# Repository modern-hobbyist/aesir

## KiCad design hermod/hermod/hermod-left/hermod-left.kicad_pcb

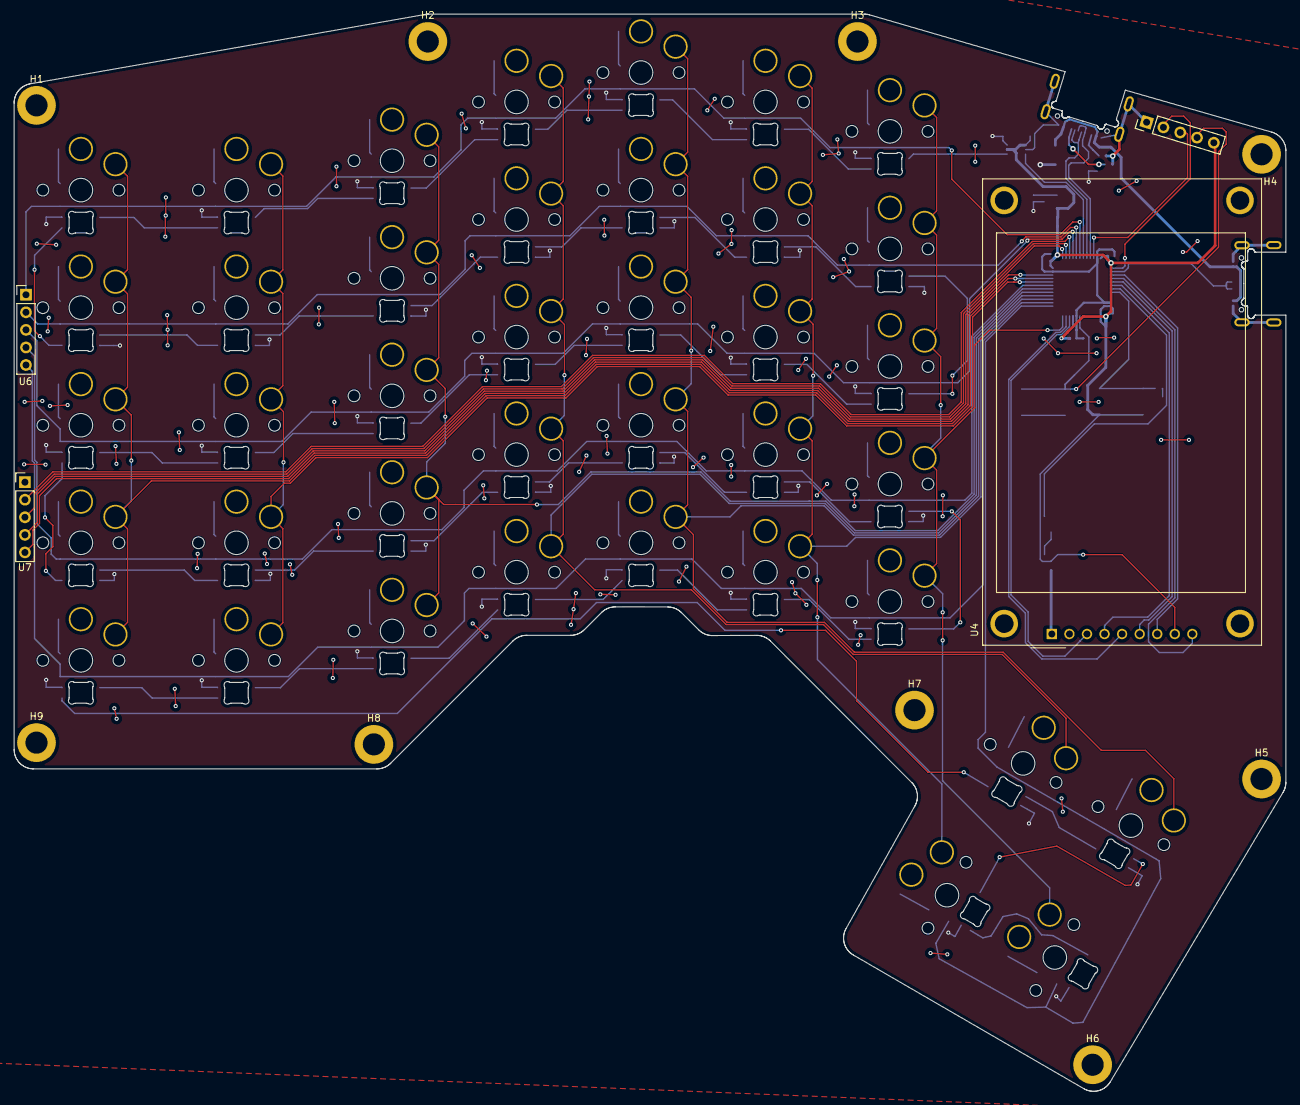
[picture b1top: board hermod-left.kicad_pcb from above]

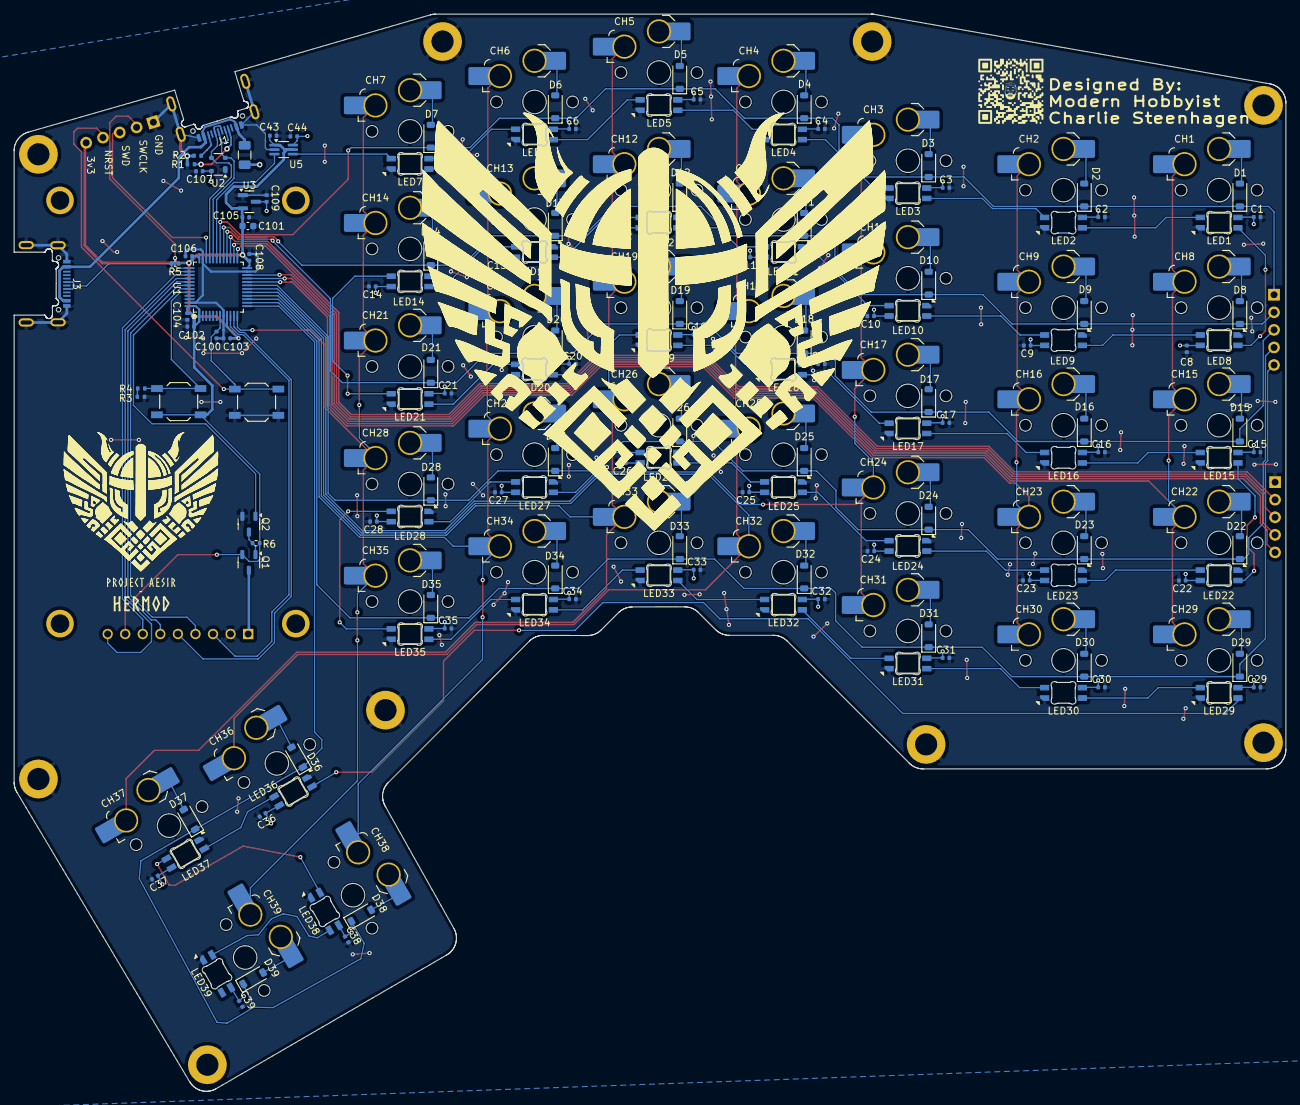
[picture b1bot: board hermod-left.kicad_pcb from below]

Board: 2 copper layers, 183.9 x 155.8 mm, 198 parts (185 on the bottom side), 119 nets.

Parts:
BOOT1: SW_SPST; SW_SPST_TL3342
C1, C2, C3, C4, C5, C6, C7, C8, C9, C10, C11, C12, C13, C14, C15, C16, C17, C18, C19, C20, C21, C22, C23, C24, C25, C26, C27, C28, C29, C30, C31, C32, C33, C34, C35, C36, C37, C38, C39, C43, C44: 0.1uF; C_0402_1005Metric
C100, C102, C103, C104, C105, C106, C109: 100nF; C_0402_1005Metric
C101: 10uF; C_0603_1608Metric
C107, C108: 1uF; C_0402_1005Metric
CH1, CH3, CH4, CH5, CH6, CH7, CH8, CH10, CH11, CH12, CH13, CH14, CH15, CH17, CH18, CH19, CH20, CH21, CH22, CH24, CH25, CH26, CH27, CH28, CH29, CH31, CH32, CH33, CH34, CH35, CH36, CH37: choc_v1_SW_HS; SW_choc_v1_HS_CPG135001S30_1u
CH2, CH9, CH16, CH23, CH30, CH38, CH39: choc_v1_SW_HS; SW_choc_v1_HS_CPG135001S30_1.5u
D1, D2, D3, D4, D5, D6, D7, D8, D9, D10, D11, D12, D13, D14, D15, D16, D17, D18, D19, D20, D21, D22, D23, D24, D25, D26, D27, D28, D29, D30, D31, D32, D33, D34, D35, D36, D37, D38, D39: D; D_SOD-123
F1: 500mA; Fuse_1206_3216Metric
H1, H2, H3, H4, H5, H6, H7, H8, H9: MountingHole_Pad; MountingHole_3.2mm_M3_DIN965_Pad
J1, J3: USB_C_Receptacle_USB2.0; USB_C_Receptacle_HRO_TYPE-C-31-M-14
J2: Conn_01x05; PinHeader_1x05_P2.54mm_Vertical
LED1, LED2, LED3, LED4, LED5, LED6, LED7, LED8, LED9, LED10, LED11, LED12, LED13, LED14, LED15, LED16, LED17, LED18, LED19, LED20, LED21, LED22, LED23, LED24, LED25, LED26, LED27, LED28, LED29, LED30, LED31, LED32, LED33, LED34, LED35, LED36, LED37, LED38, LED39: choc_SK6812MINI-E; LED_choc_6028R
Q1: AO3401A; SOT-23-3
Q2: MMUN2233LT1G; SOT-23-3
R1, R2, R3, R4, R5: 5.1k; R_0402_1005Metric
R6: 10k; R_0402_1005Metric
RST1: SW_SPST; SW_SPST_TL3342
U1: STM32F072CBT6; LQFP-48_7x7mm_P0.5mm
U2: PRTR5V0U2X; SOT-143
U3: XC6206PxxxMR-Regulator_Linear; SOT-23
U4: CR2013-MI2120
U5: TXB0101; SOT-363_SC-70-6_Handsoldering
U6, U7: Pogo_2.54mm_5p

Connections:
+3V3: BOOT1.1 (A), C43.2, C101.1, C102.1, C103.1, C104.1, C105.1, C106.1, C108.1, J2.5, Q1.2 (S), R5.1, R6.1, U1.1 (VBAT), U1.9 (VDDA), U1.24 (VDD), U1.36 (VDDIO2), U1.48 (VDD), U3.2 (VO), U4.8 (LED), U5.1 (VCCA), U5.5 (OE)
+5V: C1.1, C2.1, C3.1, C4.1, C5.1, C6.1, C7.1, C8.1, C9.1, C10.1, C11.1, C12.1, C13.1, C14.1, C15.1, C16.1, C17.1, C18.1, C19.1, C20.1, C21.1, C22.1, C23.1, C24.1, C25.1, C26.1, C27.1, C28.1, C29.1, C30.1, C31.1, C32.1, C33.1, C34.1, C35.1, C36.1, C37.1, C38.1, C39.1, C44.1, C107.1, C109.1, F1.2, LED1.1 (VDD), LED2.1 (VDD), LED3.1 (VDD), LED4.1 (VDD), LED5.1 (VDD), LED6.1 (VDD), LED7.1 (VDD), LED8.1 (VDD), LED9.1 (VDD), LED10.1 (VDD), LED11.1 (VDD), LED12.1 (VDD), LED13.1 (VDD), LED14.1 (VDD), LED15.1 (VDD), LED16.1 (VDD), LED17.1 (VDD), LED18.1 (VDD), LED19.1 (VDD), LED20.1 (VDD), LED21.1 (VDD), LED22.1 (VDD), LED23.1 (VDD), LED24.1 (VDD), LED25.1 (VDD), LED26.1 (VDD), LED27.1 (VDD), LED28.1 (VDD), LED29.1 (VDD), LED30.1 (VDD), LED31.1 (VDD), LED32.1 (VDD), LED33.1 (VDD), LED34.1 (VDD), LED35.1 (VDD), LED36.1 (VDD), LED37.1 (VDD), LED38.1 (VDD), LED39.1 (VDD), U2.4 (VCC), U3.3 (VI), U5.6 (VCCB)
BOOT0: BOOT1.2 (B), R3.1, U1.44 (BOOT0)
D+: J1.A6 (D+), J1.B6 (D+), U1.33 (PA12), U2.3 (I/O2)
D-: J1.A7 (D-), J1.B7 (D-), U1.32 (PA11), U2.2 (I/O1)
DOut1: LED1.2 (DOUT), LED8.3 (DIN)
DOut2: LED14.2 (DOUT), LED21.3 (DIN)
DOut3: LED15.2 (DOUT), LED22.3 (DIN)
DOut4: LED28.2 (DOUT), LED35.3 (DIN)
DOut5: LED29.2 (DOUT), LED36.3 (DIN)
GND: C1.2, C2.2, C3.2, C4.2, C5.2, C6.2, C7.2, C8.2, C9.2, C10.2, C11.2, C12.2, C13.2, C14.2, C15.2, C16.2, C17.2, C18.2, C19.2, C20.2, C21.2, C22.2, C23.2, C24.2, C25.2, C26.2, C27.2, C28.2, C29.2, C30.2, C31.2, C32.2, C33.2, C34.2, C35.2, C36.2, C37.2, C38.2, C39.2, C43.1, C44.2, C100.2, C101.2, C102.2, C103.2, C104.2, C105.2, C106.2, C107.2, C108.2, C109.2, H1.1, H2.1, H3.1, H4.1, H5.1, H6.1, H7.1, H8.1, H9.1, J1.A1 (GND), J1.A12 (GND), J1.B1 (GND), J1.B12 (GND), J1.S1 (SHIELD), J2.1, J3.A1 (GND), J3.A12 (GND), J3.B1 (GND), J3.B12 (GND), J3.S1 (SHIELD), LED1.4 (VSS), LED2.4 (VSS), LED3.4 (VSS), LED4.4 (VSS), LED5.4 (VSS), LED6.4 (VSS), LED7.4 (VSS), LED8.4 (VSS), LED9.4 (VSS), LED10.4 (VSS), LED11.4 (VSS), LED12.4 (VSS), LED13.4 (VSS), LED14.4 (VSS), LED15.4 (VSS), LED16.4 (VSS), LED17.4 (VSS), LED18.4 (VSS), LED19.4 (VSS), LED20.4 (VSS), LED21.4 (VSS), LED22.4 (VSS), LED23.4 (VSS), LED24.4 (VSS), LED25.4 (VSS), LED26.4 (VSS), LED27.4 (VSS), LED28.4 (VSS), LED29.4 (VSS), LED30.4 (VSS), LED31.4 (VSS), LED32.4 (VSS), LED33.4 (VSS), LED34.4 (VSS), LED35.4 (VSS), LED36.4 (VSS), LED37.4 (VSS), LED38.4 (VSS), LED39.4 (VSS), Q2.2 (E), R1.1, R2.2, R4.2, RST1.2 (B), U1.8 (VSSA), U1.23 (VSS), U1.35 (VSS), U1.47 (VSS), U2.1 (GND), U3.1 (GND), U4.2 (GND), U5.2 (GND), U7.1
LCD_CS: U1.10 (PA0), U4.3 (~CS)
LCD_DC: U1.11 (PA1), U4.5 (D/~C)
LCD_EN: Q2.1 (B), U1.43 (PB7)
LCD_MISO: U1.40 (PB4), U4.9 (MISO)
LCD_MOSI: U1.41 (PB5), U4.6 (MOSI)
LCD_PWR: Q1.3 (D), U4.1 (VCC)
LCD_RST: U1.42 (PB6), U4.4 (RESET)
LCD_SCK: U1.39 (PB3), U4.7 (SCK)
NRST: C100.1, J2.4, RST1.1 (A), U1.7 (NRST)
unnamed: CH1.2, D1.2 (A)
unnamed: CH2.2, D2.2 (A)
unnamed: CH3.2, D3.2 (A)
unnamed: CH4.2, D4.2 (A)
unnamed: CH5.2, D5.2 (A)
unnamed: CH6.2, D6.2 (A)
unnamed: CH7.2, D7.2 (A)
unnamed: CH8.2, D8.2 (A)
unnamed: CH9.2, D9.2 (A)
unnamed: CH10.2, D10.2 (A)
unnamed: CH11.2, D11.2 (A)
unnamed: CH12.2, D12.2 (A)
unnamed: CH13.2, D13.2 (A)
unnamed: CH14.2, D14.2 (A)
unnamed: CH15.2, D15.2 (A)
unnamed: CH16.2, D16.2 (A)
unnamed: CH17.2, D17.2 (A)
unnamed: CH18.2, D18.2 (A)
unnamed: CH19.2, D19.2 (A)
unnamed: CH20.2, D20.2 (A)
unnamed: CH21.2, D21.2 (A)
unnamed: CH22.2, D22.2 (A)
unnamed: CH23.2, D23.2 (A)
unnamed: CH24.2, D24.2 (A)
unnamed: CH25.2, D25.2 (A)
unnamed: CH26.2, D26.2 (A)
unnamed: CH27.2, D27.2 (A)
unnamed: CH28.2, D28.2 (A)
unnamed: CH29.2, D29.2 (A)
unnamed: CH30.2, D30.2 (A)
unnamed: CH31.2, D31.2 (A)
unnamed: CH32.2, D32.2 (A)
unnamed: CH33.2, D33.2 (A)
unnamed: CH34.2, D34.2 (A)
unnamed: CH35.2, D35.2 (A)
unnamed: CH36.2, D36.2 (A)
unnamed: CH37.2, D37.2 (A)
unnamed: CH38.2, D38.2 (A)
unnamed: CH39.2, D39.2 (A)
unnamed: J1.A5 (CC1), R1.2
unnamed: J1.B5 (CC2), R2.1
unnamed: LED1.3 (DIN), LED2.2 (DOUT)
unnamed: LED2.3 (DIN), LED3.2 (DOUT)
unnamed: LED3.3 (DIN), LED4.2 (DOUT)
unnamed: LED4.3 (DIN), LED5.2 (DOUT)
unnamed: LED5.3 (DIN), LED6.2 (DOUT)
unnamed: LED6.3 (DIN), LED7.2 (DOUT)
unnamed: LED8.2 (DOUT), LED9.3 (DIN)
unnamed: LED9.2 (DOUT), LED10.3 (DIN)
unnamed: LED10.2 (DOUT), LED11.3 (DIN)
unnamed: LED11.2 (DOUT), LED12.3 (DIN)
unnamed: LED12.2 (DOUT), LED13.3 (DIN)
unnamed: LED13.2 (DOUT), LED14.3 (DIN)
unnamed: LED15.3 (DIN), LED16.2 (DOUT)
unnamed: LED16.3 (DIN), LED17.2 (DOUT)
unnamed: LED17.3 (DIN), LED18.2 (DOUT)
unnamed: LED18.3 (DIN), LED19.2 (DOUT)
unnamed: LED19.3 (DIN), LED20.2 (DOUT)
unnamed: LED20.3 (DIN), LED21.2 (DOUT)
unnamed: LED22.2 (DOUT), LED23.3 (DIN)
unnamed: LED23.2 (DOUT), LED24.3 (DIN)
unnamed: LED24.2 (DOUT), LED25.3 (DIN)
unnamed: LED25.2 (DOUT), LED26.3 (DIN)
unnamed: LED26.2 (DOUT), LED27.3 (DIN)
unnamed: LED27.2 (DOUT), LED28.3 (DIN)
unnamed: LED29.3 (DIN), LED30.2 (DOUT)
unnamed: LED30.3 (DIN), LED31.2 (DOUT)
unnamed: LED31.3 (DIN), LED32.2 (DOUT)
unnamed: LED32.3 (DIN), LED33.2 (DOUT)
unnamed: LED33.3 (DIN), LED34.2 (DOUT)
unnamed: LED34.3 (DIN), LED35.2 (DOUT)
unnamed: LED36.2 (DOUT), LED37.3 (DIN)
unnamed: LED37.2 (DOUT), LED38.3 (DIN)
unnamed: LED38.2 (DOUT), LED39.3 (DIN)
unnamed: Q1.1 (G), Q2.3 (C), R6.2
unnamed: R3.2, R4.1
RGB3.3: U1.31 (PA10), U5.3 (A)
RGB5v: LED7.3 (DIN), U5.4 (B)
SWCLK: J2.2, U1.37 (PA14)
SWD: J2.3, U1.34 (PA13)
SplitSerial: J3.A6 (D+), J3.B6 (D+), R5.2, U1.38 (PA15)
VBUS: F1.1, J1.A4 (VBUS), J1.A9 (VBUS), J1.B4 (VBUS), J1.B9 (VBUS), J3.A4 (VBUS), J3.A9 (VBUS), J3.B4 (VBUS), J3.B9 (VBUS)
col0: CH1.1, CH8.1, CH15.1, CH22.1, CH29.1, U1.21 (PB10)
col1: CH2.1, CH9.1, CH16.1, CH23.1, CH30.1, U1.20 (PB2)
col2: CH3.1, CH10.1, CH17.1, CH24.1, CH31.1, U1.18 (PB0)
col3: CH4.1, CH11.1, CH18.1, CH25.1, CH32.1, CH36.1, U1.17 (PA7)
col4: CH5.1, CH12.1, CH19.1, CH26.1, CH33.1, CH37.1, U1.16 (PA6)
col5: CH6.1, CH13.1, CH20.1, CH27.1, CH34.1, CH38.1, U1.15 (PA5)
col6: CH7.1, CH14.1, CH21.1, CH28.1, CH35.1, CH39.1, U1.12 (PA2)
col7: U1.22 (PB11), U7.5
col8: U1.25 (PB12), U7.4
col9: U1.26 (PB13), U7.3
col10: U1.27 (PB14), U7.2
row0: D1.1 (K), D2.1 (K), D3.1 (K), D4.1 (K), D5.1 (K), D6.1 (K), D7.1 (K), U1.30 (PA9), U6.1
row1: D8.1 (K), D9.1 (K), D10.1 (K), D11.1 (K), D12.1 (K), D13.1 (K), D14.1 (K), U1.29 (PA8), U6.2
row2: D15.1 (K), D16.1 (K), D17.1 (K), D18.1 (K), D19.1 (K), D20.1 (K), D21.1 (K), U1.28 (PB15), U6.3
row3: D22.1 (K), D23.1 (K), D24.1 (K), D25.1 (K), D26.1 (K), D27.1 (K), D28.1 (K), U1.19 (PB1), U6.4
row4: D29.1 (K), D30.1 (K), D31.1 (K), D32.1 (K), D33.1 (K), D34.1 (K), D35.1 (K), U1.14 (PA4), U6.5
row5: D36.1 (K), D37.1 (K), D38.1 (K), D39.1 (K), U1.13 (PA3)

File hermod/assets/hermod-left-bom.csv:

"Id";"Designator";"Footprint";"Quantity";"Designation";"Supplier and ref";
1;"U7,U6";"Pogo_2.54mm_5p";2;"~";;;
2;"U4";"CR2013-MI2120";1;"CR2013-MI2120";;;
3;"J2";"PinHeader_1x05_P2.54mm_Vertical";1;"Conn_01x05";;;
4;"CH17,CH14,CH33,CH11,CH12,CH21,CH5,CH6,CH31,CH26,CH24,CH27,CH25,CH20,CH7,CH8,CH1,CH19,CH10,CH34,CH22,CH3,CH36,CH4,CH13,CH29,CH35,CH18,CH15,CH37,CH32,CH28";"SW_choc_v1_HS_CPG135001S30_1u";32;"choc_v1_SW_HS";;;
5;"LED36,LED13,LED21,LED32,LED23,LED2,LED20,LED1,LED38,LED29,LED33,LED30,LED18,LED19,LED17,LED8,LED39,LED15,LED24,LED16,LED3,LED4,LED5,LED26,LED27,LED31,LED25,LED9,LED12,LED22,LED34,LED6,LED10,LED11,LED7,LED35,LED28,LED14,LED37";"LED_choc_6028R";39;"choc_SK6812MINI-E";;;
6;"D2,D33,D28,D20,D1,D36,D30,D22,D39,D14,D24,D13,D12,D19,D16,D25,D11,D3,D37,D15,D18,D23,D34,D21,D6,D5,D35,D4,D31,D29,D38,D10,D26,D8,D17,D7,D32,D9,D27";"D_SOD-123";39;"D";;;
7;"C106,C104,C109,C100,C102,C105,C103";"C_0402_1005Metric";7;"100nF";;;
8;"C10,C28,C19,C43,C11,C20,C34,C33,C44,C36,C23,C27,C32,C22,C21,C6,C37,C14,C3,C39,C18,C9,C7,C15,C30,C38,C24,C29,C25,C4,C26,C35,C8,C12,C16,C5,C17,C31,C1,C13,C2";"C_0402_1005Metric";41;"0.1uF";;;
9;"Q1";"SOT-23-3";1;"AO3401A";;;
10;"CH16,CH38,CH23,CH30,CH2,CH39,CH9";"SW_choc_v1_HS_CPG135001S30_1.5u";7;"choc_v1_SW_HS";;;
11;"RST1,BOOT1";"SW_SPST_TL3342";2;"SW_SPST";;;
12;"R2,R3,R1,R4";"R_0402_1005Metric";4;"5.1k";;;
13;"C101";"C_0603_1608Metric";1;"10uF";;;
14;"C107,C108";"C_0402_1005Metric";2;"1uF";;;
15;"F1";"Fuse_1206_3216Metric";1;"500mA";;;
16;"U5";"SOT-363_SC-70-6_Handsoldering";1;"TXB0101";;;
17;"U2";"SOT-143";1;"PRTR5V0U2X";;;
18;"U1";"LQFP-48_7x7mm_P0.5mm";1;"STM32F072CBT6";;;
19;"J1,J3";"USB_C_Receptacle_HRO_TYPE-C-31-M-14";2;"USB_C_Receptacle_USB2.0";;;
20;"U3";"SOT-23";1;"XC6206PxxxMR-Regulator_Linear";;;
21;"Q2";"SOT-23-3";1;"MMUN2233LT1G";;;

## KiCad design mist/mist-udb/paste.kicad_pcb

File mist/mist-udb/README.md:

# Mist

**Mist** is my take on a full size keyboard, but with some upgrades I carried over from my second keyboard build--**[Hermod](https://github.com/modern-hobbyist/aesir/tree/main/hermod-mk2)**. Furthermore, this is the UDB version of **Mist**, which stands for Unified Daughter Board

Aside from the UDB connector and the lack of USB-C/on-board ESD protection circuitry, this keyboard is functionally identical to the base **Mist** keyboard.

This project is open source, so I'll do my best to keep it updated as questions come in. I can't guarantee I'll always have time to respond, but if you have questions you can reach out on [my Discord server](https://discord.gg/68WXGsjqJp) or on the [Keyboard Atelier Discord](https://discord.gg/b7vwhHS).

## Why?

1. First of all, I'm addicted to designing custom keyboards now, so jot that down.
2. I have two children now, and while I love my split keyboard, typing with one hand is 100 times more difficult and time consuming on a split.
3. Related to above, I wanted a keyboard that would appeal to the non-split community, but also incorporated all the features I loved mose about my split build.

## Features

- **2.2" LCD Display**: A 2.2" LCD Display to show keyboard state, stats, and any fun animations I can think of.
- **Thumb Clusters in Place of Spacebar**: I loved the thumb clusters from my split keyboard and the giant spacebar is such a waste of space!
- **Connector for Unified Daughter Board**: A Unified Daughter Board extracts all the ESD and over-voltage protection from the main PCB and allows for more complex case shapes.
- **Per-Key RGB Lighting**: Vibrant, individually addressable RGB LEDs for endless customization.
- **KS-33 + MX/Gateron Normal Profile Hot-Swappable Switch Sockets**: Support for either KS-33 low-profile or MX style (Cherry or Gateron Normal profile) switches.
- **QMK Firmware**: Fully programmable and customizable using QMK.
- **Standard QWERTY Layout and Keymap**: The layout we all grew up learning to type on!

## Specifications

- **Microcontroller**: STM32G474RETx
- **Display**: 2.2" LCD (320x240 resolution) per half.
- **Lighting**: SK6812 Mini RGB LEDs.

## BOM
> Note: I have not finished building a KS-33 version of this keyboard. However, the only difference is the hotswap sockets you use (and the corresponding switches/keycaps). Also, there shouldn't be any issue using the existing case design with the KS-33 version.

### Electronics

- [Digikey Parts LIst](https://www.digikey.com/en/mylists/list/XUNNWUFIT7)
- [ILI9341 LCD](https://www.aliexpress.us/item/2255800032844649.html?spm=a2g0o.order_list.order_list_main.107.32781802UqhhF2&gatewayAdapt=glo2usa)
- [PCBWay Project](https://www.pcbway.com/project/shareproject/Custom_Mechanical_Keyboard_7a40c23a.html)
  - > Note: If you are ordering assembled PCBs from the PCBWay Project, it may take a few cycles to smooth out any BOM hiccups.
- [Unified Daughter Board](https://cannonkeys.com/products/unified-daughterboard-and-jst-cable?variant=41613867843695)
- [Hotswap Sockets I used](https://www.aliexpress.us/item/3256807081236706.html?spm=a2g0o.order_list.order_list_main.5.32781802UqhhF2&gatewayAdapt=glo2usa)
- [Keycaps I used](https://www.aliexpress.us/item/3256805029855838.html?spm=a2g0o.order_list.order_list_main.16.32781802UqhhF2&gatewayAdapt=glo2usa)
- [Switches of Choice](https://a.co/d/3fji9Gi)
- [Stabilizers of CHoice](https://a.co/d/hJjX7h8)

### Hardware

- [1.5mm Acrylic Sheet](https://a.co/d/8NMezDu)
- [M3x8mm Bolts - x13](https://boltdepot.com/Product-Details?product=13635)
- [M3 Nuts - x4](https://boltdepot.com/Product-Details?product=4773)
- [Heatset Inserts - M3x3mm](https://a.co/d/18Dypq1)
- [3mm Poron Sheet](https://www.aliexpress.us/item/3256804497716681.html?spm=a2g0o.order_list.order_list_main.52.32781802UqhhF2&gatewayAdapt=glo2usa)
- [18x3x3mm gaskets](https://www.aliexpress.us/item/3256804012735285.html?spm=a2g0o.cart.0.0.1c1138daK1mQRd&mp=1&pdp_npi=5%40dis%21USD%21USD%202.36%21USD%202.36%21%21USD%202.36%21%21%21%40210311cc17636591867721894e25ec%2112000035892927121%21ct%21US%213601384632%21%211%210&_gl=1*1bh33c8*_gcl_au*MjAxNDU4NTA1NS4xNzYzNjU4NjIz*_ga*NTI5MjE4NDcxLjE3NjA5Nzk3NTM.*_ga_VED1YSGNC7*czE3NjM2NTg2MjMkbzMkZzEkdDE3NjM2NTkxODckajM4JGwwJGgw&gatewayAdapt=glo2usa)
- [M2x6mm Nylon Standoffs](https://www.aliexpress.us/item/3256808418665069.html?spm=a2g0o.order_list.order_list_main.37.32781802UqhhF2&gatewayAdapt=glo2usa) - Female - Female
- [M2x3mm screws](https://www.aliexpress.us/item/3256807746050750.html?spm=a2g0o.order_list.order_list_main.32.32781802UqhhF2&gatewayAdapt=glo2usa)
- [8mm Steel Rods](https://a.co/d/39idH9k)

# Tools

- [Heat Set Insert tips](https://a.co/d/3we9tOl)
- 3d Printer
- Allen Wrenches
- Razor Blade
- Soldering Iron
- Computer
- USB C Cable
- Super Glue

## License

This project is licensed under the MIT License. See the [LICENSE](../LICENSE) file for details.

## Acknowledgments

- The QMK community for their amazing firmware.
- Adafruit for the GFX library support.
- Inspiration from the mechanical keyboard enthusiast community.

---

For more information, check out the [Modern Hobbyist YouTube channel](https://www.youtube.com/ModernHobbyist) for videos about this project!

> Also, please let me know in an issue or on Discord if there are issues with this board or the supplementary files so I can get them updated!

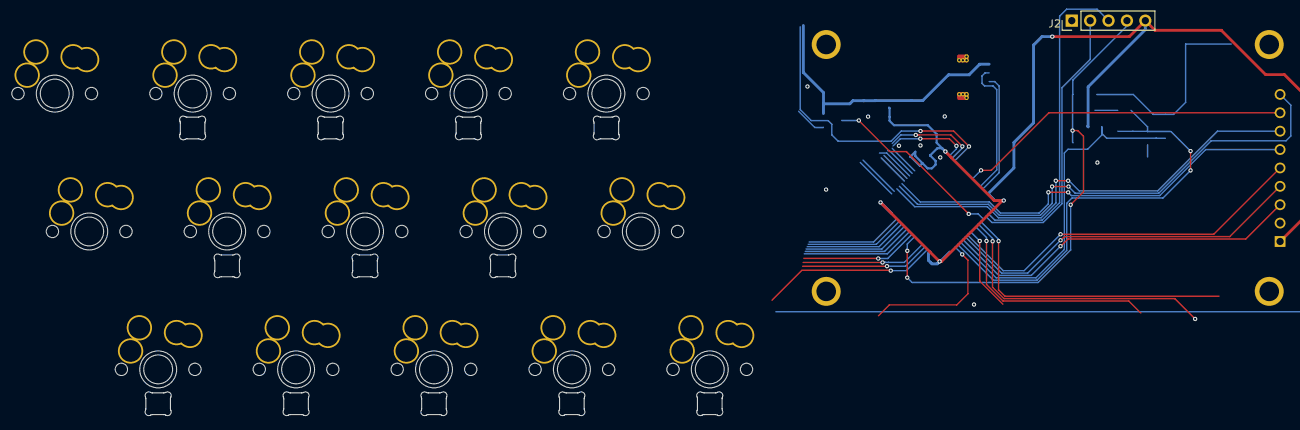
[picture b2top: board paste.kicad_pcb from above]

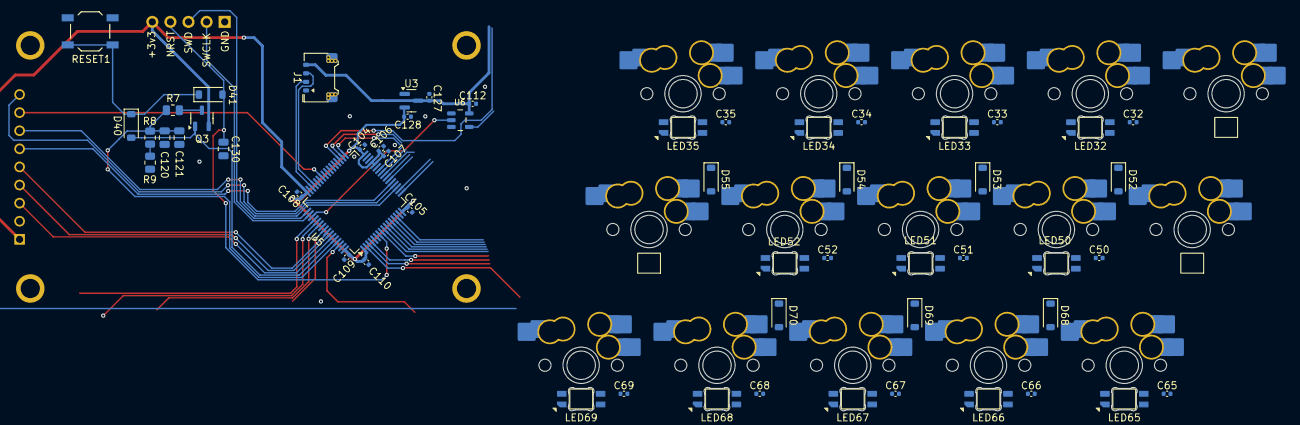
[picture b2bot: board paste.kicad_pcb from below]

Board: 2 copper layers, 72 parts (70 on the bottom side), 44 nets.

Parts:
C32, C33, C34, C35, C50, C51, C52, C65, C66, C67, C68, C69, C112: 0.1uF; C_0402_1005Metric
C104, C105, C106, C107, C108, C109, C110: 100nF; C_0402_1005Metric
C120, C121, C130: 100n; C_0805_2012Metric
C127, C128: 1uF; C_0402_1005Metric
CH31, CH32, CH33, CH34, CH35, CH49, CH50, CH51, CH52, CH53, CH65, CH66, CH67, CH68, CH69: KS33_SW_HS; KS-33_MX-Hotswap-1U
D40, D41: 1N4148; D_SOD-123
D52, D53, D54, D55, D68, D69, D70: D; D_SOD-123
J1: 78171-0004; Molex_Pico-EZmate_78171-0004_1x04-1MP_P1.20mm_Vertical
J2: Conn_01x05; PinHeader_1x05_P2.54mm_Vertical
LED32, LED33, LED34, LED35, LED50, LED51, LED52, LED65, LED66, LED67, LED68, LED69: choc_SK6812MINI-E; LED_choc_6028R
Q3: MMUN2133LT1G; SOT-23-3
R7: 120; R_0805_2012Metric
R8, R9: 68k; R_0805_2012Metric
RESET1: DFU; SW_SPST_TL3342
U3: XC6206PxxxMR-Regulator_Linear; SOT-23
U4: CR2013-MI2120
U5: STM32G474RETx; LQFP-64_10x10mm_P0.5mm
U6: SN74AHCT1G125DBVR; SOT95P280X145-5N

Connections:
+3V3: C104.1, C105.1, C106.1, C107.1, C108.1, C109.1, C110.1, C128.1, J2.5, Q3.2 (E), U3.2 (VO), U4.1 (VCC), U5.1 (VBAT), U5.16 (VDD), U5.28 (VREF+), U5.29 (VDDA), U5.32 (VDD), U5.48 (VDD), U5.64 (VDD)
+5V: C32.1, C33.1, C34.1, C35.1, C50.1, C51.1, C52.1, C65.1, C66.1, C67.1, C68.1, C69.1, C112.1, C127.1, J1.4, LED32.1 (VDD), LED33.1 (VDD), LED34.1 (VDD), LED35.1 (VDD), LED50.1 (VDD), LED51.1 (VDD), LED52.1 (VDD), LED65.1 (VDD), LED66.1 (VDD), LED67.1 (VDD), LED68.1 (VDD), LED69.1 (VDD), U3.3 (VI), U6.5 (VCC)
BOOT0: C120.2, C121.2, R7.2, R8.2, U5.61 (PB8)
BOOT0_CHRG: D40.2 (A), Q3.1 (B), U5.60 (PB7)
D+: J1.2, U5.46 (PA12)
D-: J1.3, U5.45 (PA11)
GND: C32.2, C33.2, C34.2, C35.2, C50.2, C51.2, C52.2, C65.2, C66.2, C67.2, C68.2, C69.2, C104.2, C105.2, C106.2, C107.2, C108.2, C109.2, C110.2, C112.2, C120.1, C121.1, C127.2, C128.2, C130.1, J1.1, J1.MP (MountPin), J2.1, LED32.4 (VSS), LED33.4 (VSS), LED34.4 (VSS), LED35.4 (VSS), LED50.4 (VSS), LED51.4 (VSS), LED52.4 (VSS), LED65.4 (VSS), LED66.4 (VSS), LED67.4 (VSS), LED68.4 (VSS), LED69.4 (VSS), R9.2, RESET1.1, U3.1 (GND), U4.2 (GND), U5.15 (VSS), U5.27 (VSSA), U5.31 (VSS), U5.47 (VSS), U5.63 (VSS), U6.1 (~OE), U6.3 (GND)
LCD_BL_PWM: U4.8 (LED), U5.42 (PA8)
LCD_CS: U4.3 (~CS), U5.59 (PB6)
LCD_DC: U4.5 (D/~C), U5.57 (PB4)
LCD_MISO: U4.9 (MISO), U5.20 (PA6)
LCD_MOSI: U4.6 (MOSI), U5.21 (PA7)
LCD_RST: U4.4 (RESET), U5.58 (PB5)
LCD_SCK: U4.7 (SCK), U5.19 (PA5)
NRST: C130.2, D41.2 (A), J2.4, U5.7 (PG10)
unnamed: D40.1 (K), D41.1 (K), RESET1.2
unnamed: CH50.2, D52.2 (A)
unnamed: CH51.2, D53.2 (A)
unnamed: CH52.2, D54.2 (A)
unnamed: CH53.2, D55.2 (A)
unnamed: CH66.2, D68.2 (A)
unnamed: CH67.2, D69.2 (A)
unnamed: CH68.2, D70.2 (A)
unnamed: LED32.3 (DIN), LED33.2 (DOUT)
unnamed: LED33.3 (DIN), LED34.2 (DOUT)
unnamed: LED34.3 (DIN), LED35.2 (DOUT)
unnamed: LED50.2 (DOUT), LED51.3 (DIN)
unnamed: LED51.2 (DOUT), LED52.3 (DIN)
unnamed: LED65.3 (DIN), LED66.2 (DOUT)
unnamed: LED66.3 (DIN), LED67.2 (DOUT)
unnamed: LED67.3 (DIN), LED68.2 (DOUT)
unnamed: LED68.3 (DIN), LED69.2 (DOUT)
unnamed: Q3.3 (C), R7.1
unnamed: R8.1, R9.1
RGB3.3: U5.51 (PA15), U6.2 (A)
SWCLK: J2.2, U5.50 (PA14)
SWD: J2.3, U5.49 (PA13)
col2: CH31.1, CH49.1, CH65.1, U5.26 (PB2)
col3: CH32.1, CH50.1, CH66.1, U5.25 (PB1)
col4: CH33.1, CH51.1, CH67.1, U5.24 (PB0)
col5: CH34.1, CH52.1, CH68.1, U5.23 (PC5)
col6: CH35.1, CH53.1, CH69.1, U5.22 (PC4)
row3: D52.1 (K), D53.1 (K), D54.1 (K), D55.1 (K), U5.2 (PC13)
row4: D68.1 (K), D69.1 (K), D70.1 (K), U5.3 (PC14)
